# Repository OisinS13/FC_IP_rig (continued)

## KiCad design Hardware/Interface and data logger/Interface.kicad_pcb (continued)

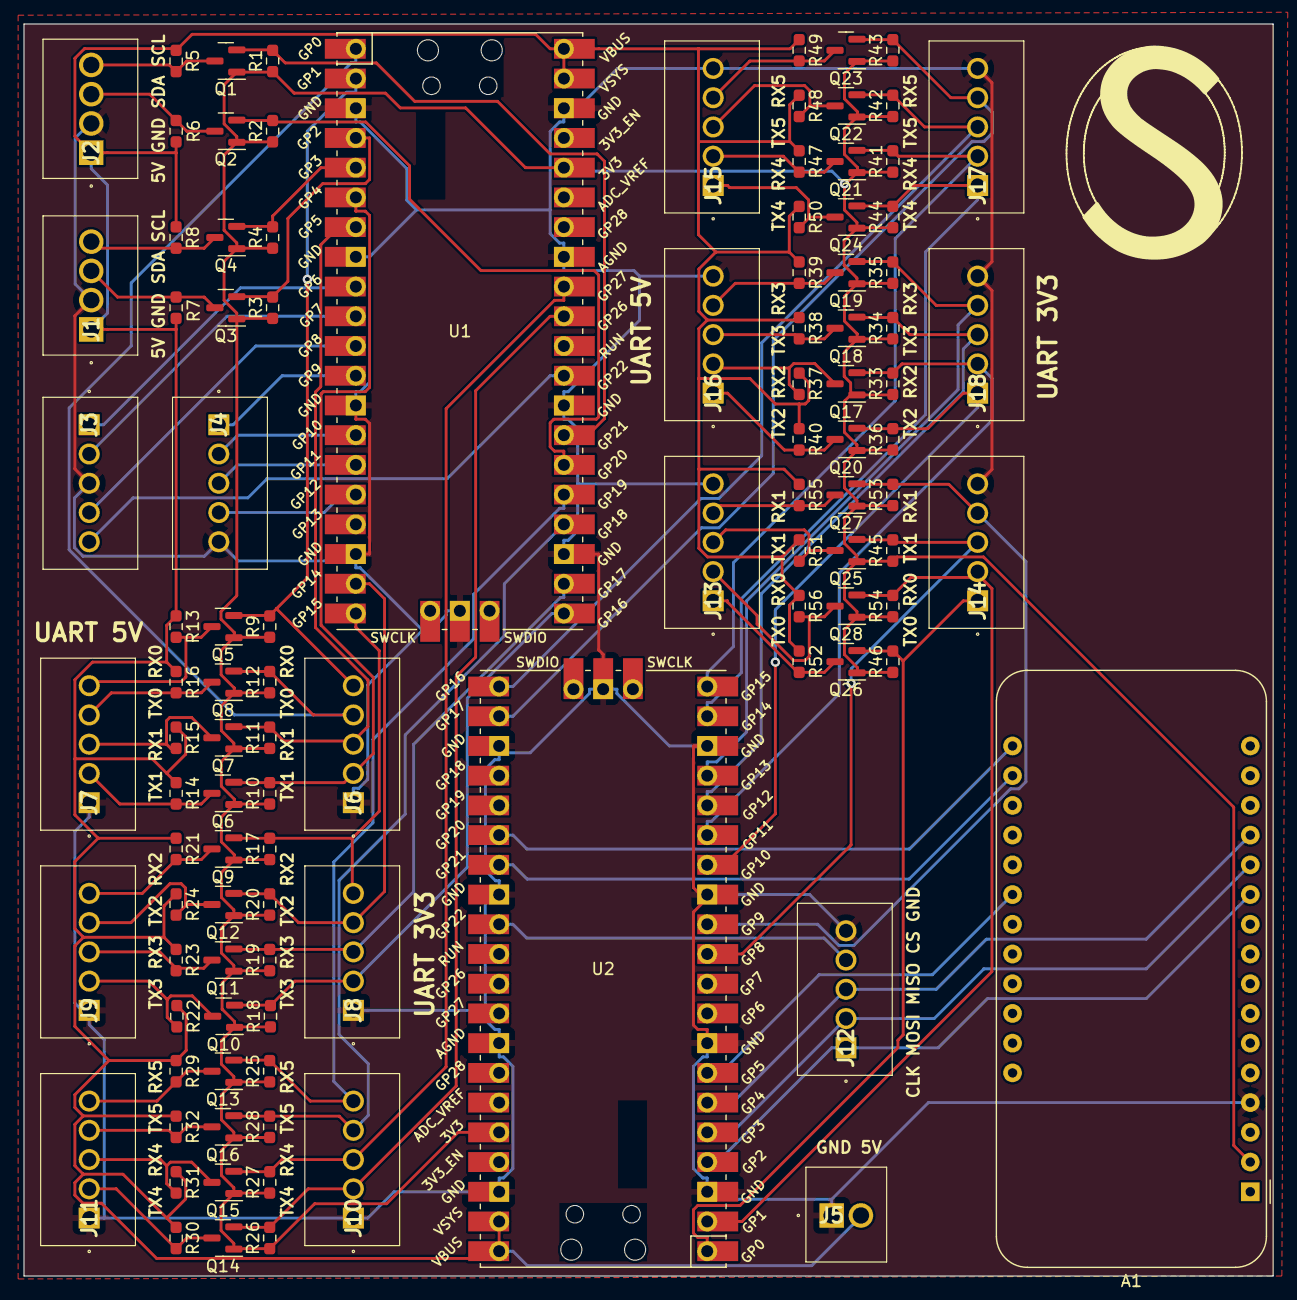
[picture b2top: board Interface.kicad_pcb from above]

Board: 2 copper layers, 106.8 x 107.0 mm, 105 parts (0 on the bottom side), 74 nets.

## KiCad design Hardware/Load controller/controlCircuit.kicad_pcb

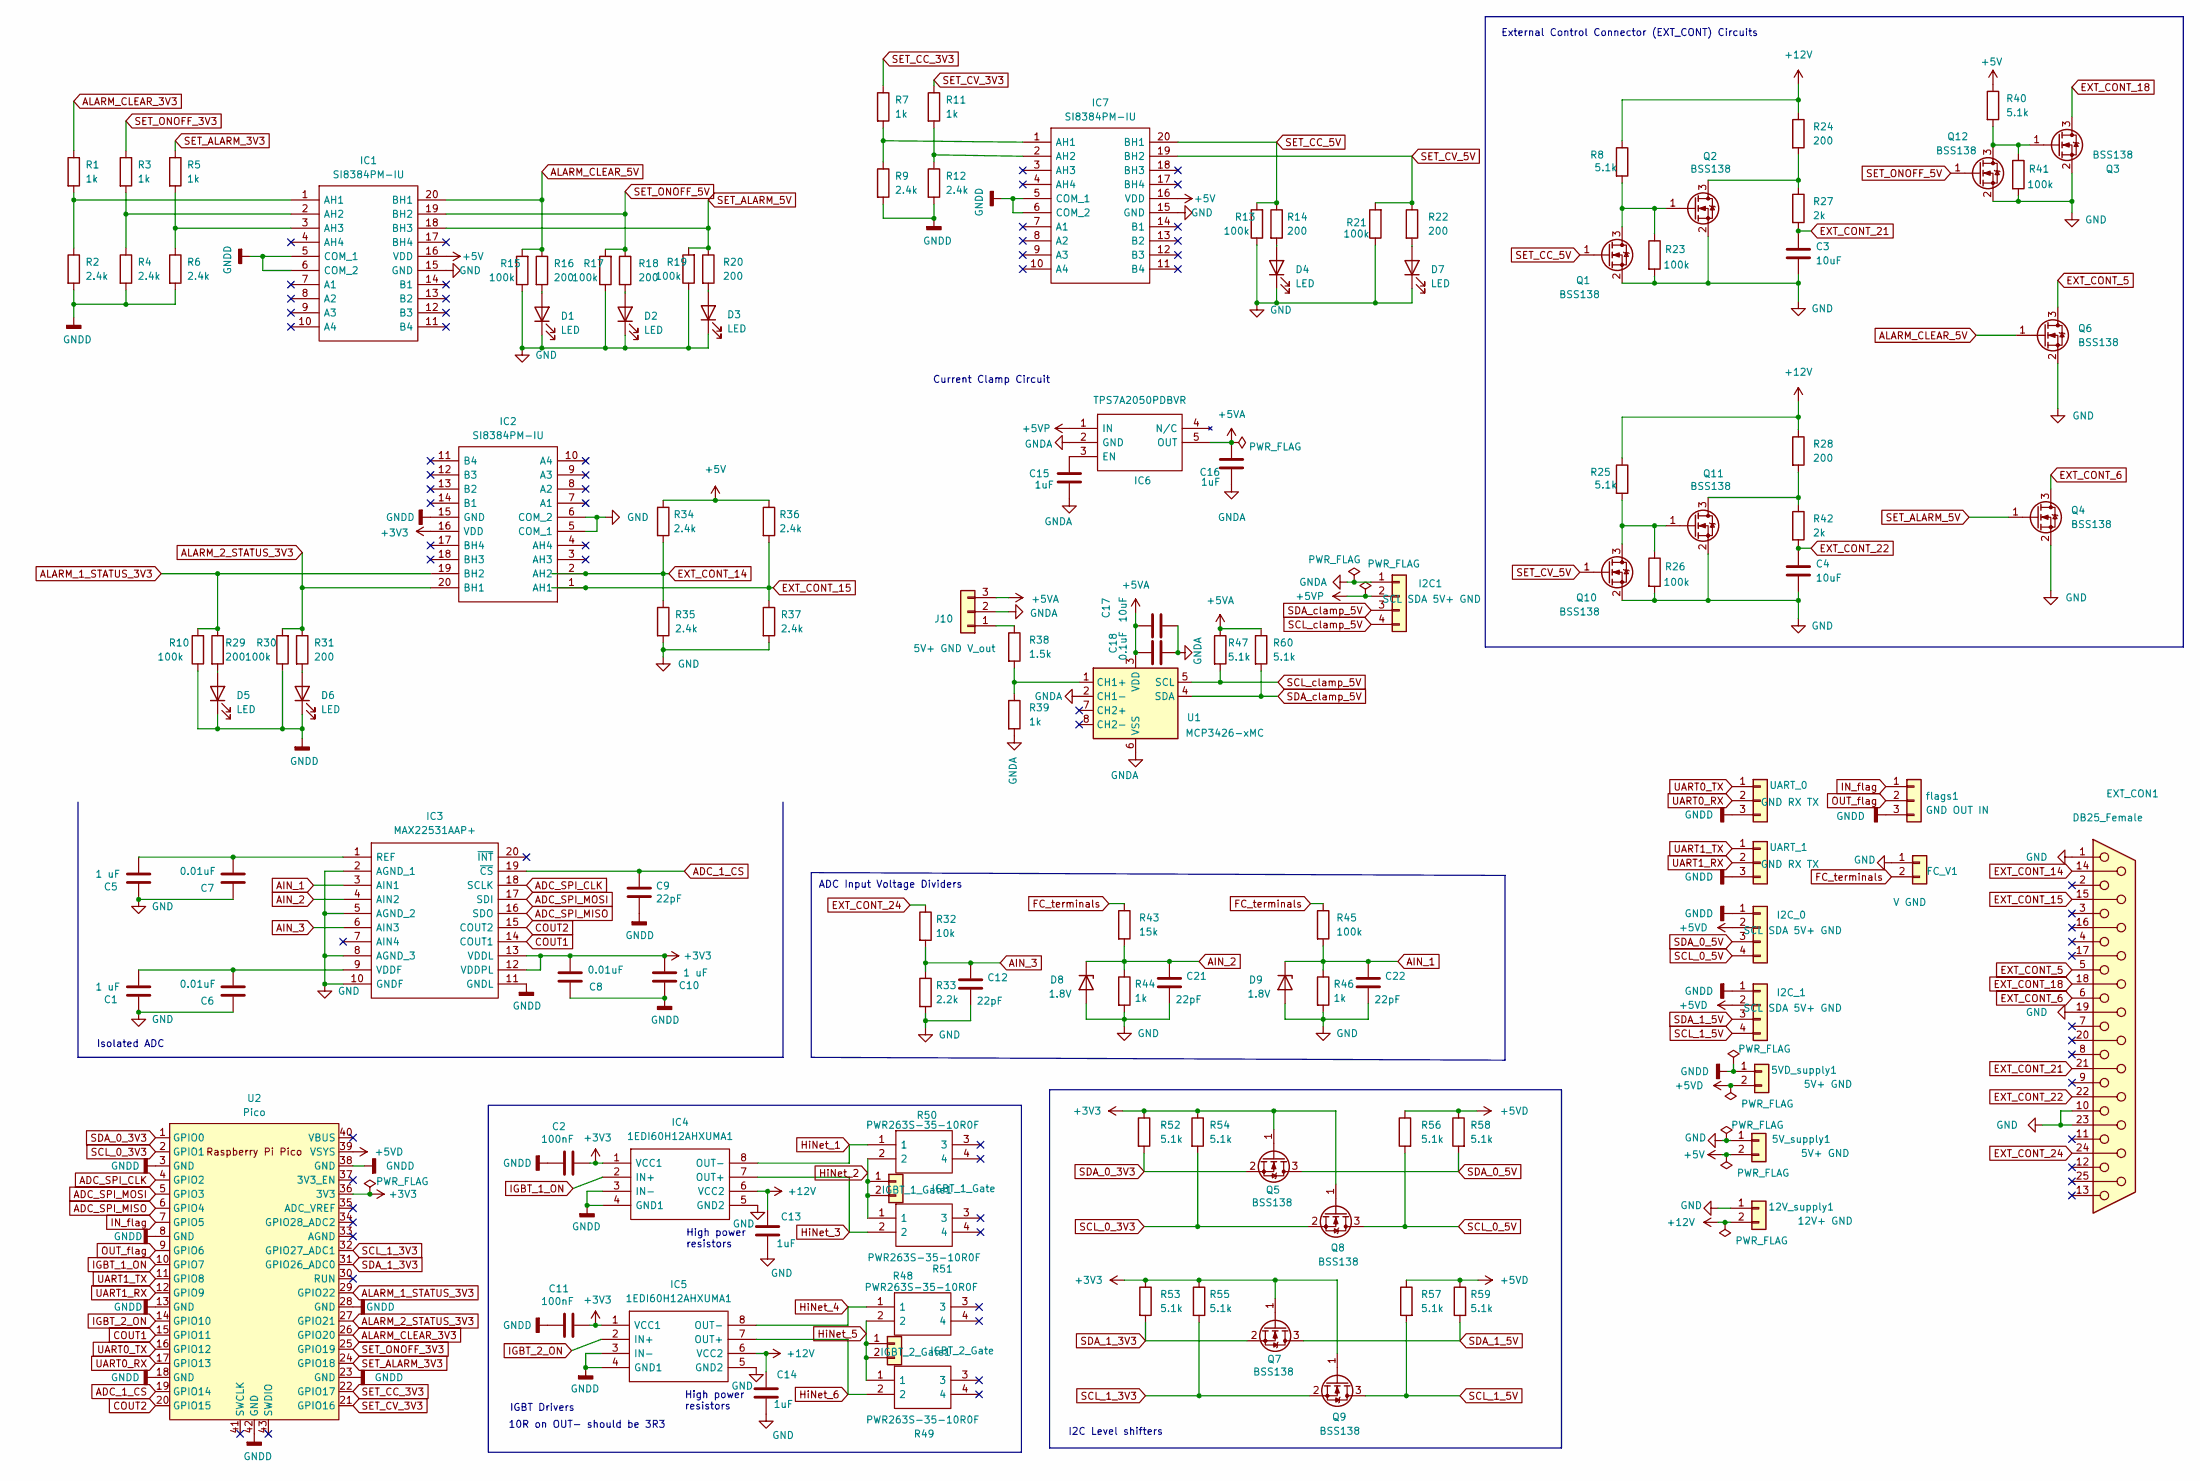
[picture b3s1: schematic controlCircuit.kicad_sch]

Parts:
5VD_supply1, 5V_supply1: 5V+ GND; 1963531
12V_supply1: 12V+ GND; 1963531
C1, C5, C10: 1 uF; C_0603_1608Metric_Pad1.08x0.95mm_HandSolder
C2, C11: 100nF; C_0603_1608Metric_Pad1.08x0.95mm_HandSolder
C3, C4: 10uF; CP_Radial_D4.0mm_P2.00mm
C6, C7, C8: 0.01uF; C_0603_1608Metric_Pad1.08x0.95mm_HandSolder
C9, C12, C21, C22: 22pF; C_0603_1608Metric_Pad1.08x0.95mm_HandSolder
C13, C14, C15, C16: 1uF; C_0603_1608Metric_Pad1.08x0.95mm_HandSolder
C17: 10uF; C_0603_1608Metric_Pad1.08x0.95mm_HandSolder
C18: 0.1uF; C_0603_1608Metric_Pad1.08x0.95mm_HandSolder
D1, D2, D3, D4, D5, D6, D7: LED; LED_0603_1608Metric_Pad1.05x0.95mm_HandSolder
D8, D9: 1.8V; SOD3716X135N
EXT_CON1: DB25_Female; ID25S33E4GX00LF
FC_V1: V GND; 1963531
I2C1, I2C_0, I2C_1: SCL SDA 5V+ GND; 1963557
IC1, IC2, IC7: SI8384PM-IU; SOP64P600X175-20N; Mouser Part Number 634-SI8384PM-IU
IC3: MAX22531AAP+; SOP65P778X199-20N; Mouser Part Number 700-MAX22531AAP+
IC4, IC5: 1EDI60H12AHXUMA1; SOIC127P1030X265-8N; Mouser Part Number 726-1EDI60H12AHXUMA1
IC6: TPS7A2050PDBVR; SOT95P280X145-5N; Mouser Part Number 595-TPS7A2050PDBVR
IGBT_1_Gate1: IGBT_1_Gate; 1963531
IGBT_2_Gate1: IGBT_2_Gate; 1963531
J10: 5V+ GND V_out; L06P400S05_footprint
Q1, Q2, Q3, Q4, Q5, Q6, Q7, Q8, Q9, Q10, Q11, Q12: BSS138; SOT-23
R1, R3, R5, R7, R11, R39, R44, R46: 1k; R_0603_1608Metric_Pad0.98x0.95mm_HandSolder
R2, R4, R6, R9, R12, R34, R35, R36, R37: 2.4k; R_0603_1608Metric_Pad0.98x0.95mm_HandSolder
R8, R25, R40, R47, R52, R53, R54, R55, R56, R57, R58, R59, R60: 5.1k; R_0603_1608Metric_Pad0.98x0.95mm_HandSolder
R10, R13, R15, R17, R19, R21, R23, R26, R30, R41, R45: 100k; R_0603_1608Metric_Pad0.98x0.95mm_HandSolder
R14, R16, R18, R20, R22, R24, R28, R29, R31: 200; R_0603_1608Metric_Pad0.98x0.95mm_HandSolder
R27, R42: 2k; R_0603_1608Metric_Pad0.98x0.95mm_HandSolder
R32: 10k; R_0603_1608Metric_Pad0.98x0.95mm_HandSolder
R33: 2.2k; R_0603_1608Metric_Pad0.98x0.95mm_HandSolder
R38: 1.5k; R_0603_1608Metric_Pad0.98x0.95mm_HandSolder
R43: 15k; R_0603_1608Metric_Pad0.98x0.95mm_HandSolder
R48, R49, R50, R51: PWR263S-35-10R0F; PWR263S3510R0F; Mouser Part Number 652-PWR263S3510R0F
U1: MCP3426-xMC; DFN-8-1EP_3x2mm_P0.5mm_EP1.75x1.45mm
U2: Pico; RPi_Pico_SMD_TH
UART_0, UART_1: GND RX TX; 1963544
flags1: GND OUT IN; 1963544

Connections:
+3V3: C2.2, C8.2, C10.1, C11.2, IC2.16 (VDD), IC3.12 (VDDPL), IC3.13 (VDDL), IC4.1 (VCC1), IC5.1 (VCC1), Q5.1 (G), Q7.1 (G), Q8.1 (G), Q9.1 (G), R52.1, R53.1, R54.1, R55.1, U2.36 (3V3)
+5V: 5V_supply1.2, IC1.16 (VDD), IC7.16 (VDD), R34.1, R36.1, R40.1
+5VA: C16.1, C17.1, C18.1, IC6.5 (OUT), J10.3, R47.1, R60.1, U1.3 (VDD)
+5VD: 5VD_supply1.2, I2C_0.2, I2C_1.2, R56.1, R57.1, R58.1, R59.1, U2.39 (VSYS)
+5VP: I2C1.2, IC6.1 (IN)
+12V: 12V_supply1.2, C13.1, C14.1, IC4.6 (VCC2), IC5.6 (VCC2), R8.1, R24.1, R25.1, R28.1
ADC_1_CS: C9.1, IC3.19 (~CS), U2.19 (GPIO14)
ADC_SPI_CLK: IC3.18 (SCLK), U2.4 (GPIO2)
ADC_SPI_MISO: IC3.16 (SDO), U2.6 (GPIO4)
ADC_SPI_MOSI: IC3.17 (SDI), U2.5 (GPIO3)
AIN_1: C22.1, D9.1 (K), IC3.3 (AIN1), R45.2, R46.1
AIN_2: C21.1, D8.1 (K), IC3.4 (AIN2), R43.2, R44.1
AIN_3: C12.1, IC3.6 (AIN3), R32.2, R33.1
ALARM_1_STATUS_3V3: IC2.19 (BH2), R10.2, R29.1, U2.29 (GPIO22)
ALARM_2_STATUS_3V3: IC2.20 (BH1), R30.2, R31.1, U2.27 (GPIO21)
ALARM_CLEAR_3V3: R1.1, U2.26 (GPIO20)
ALARM_CLEAR_5V: IC1.20 (BH1), Q6.1 (G), R15.2, R16.1
COUT1: IC3.14 (COUT1), U2.15 (GPIO11)
COUT2: IC3.15 (COUT2), U2.20 (GPIO15)
EXT_CONT_5: EXT_CON1.5, Q6.3 (D)
EXT_CONT_6: EXT_CON1.6, Q4.3 (D)
EXT_CONT_14: EXT_CON1.14, IC2.2 (AH2), R34.2, R35.1
EXT_CONT_15: EXT_CON1.15, IC2.1 (AH1), R36.2, R37.1
EXT_CONT_18: EXT_CON1.18, Q3.3 (D)
EXT_CONT_21: C3.1, EXT_CON1.21, R27.2
EXT_CONT_22: C4.1, EXT_CON1.22, R42.2
EXT_CONT_24: EXT_CON1.24, R32.1
FC_terminals: FC_V1.2, R43.1, R45.1
GND: 5V_supply1.1, 12V_supply1.1, C1.2, C3.2, C4.2, C5.2, C6.1, C7.1, C12.2, C13.2, C14.2, C21.2, C22.2, D1.1 (K), D2.1 (K), D3.1 (K), D4.1 (K), D7.1 (K), D8.2 (A), D9.2 (A), EXT_CON1.1, EXT_CON1.10, EXT_CON1.19, EXT_CON1.23, FC_V1.1, IC1.15 (GND), IC2.5 (COM_1), IC2.6 (COM_2), IC3.2 (AGND_1), IC3.5 (AGND_2), IC3.8 (AGND_3), IC3.10 (GNDF), IC4.5 (GND2), IC5.5 (GND2), IC7.15 (GND), Q1.2 (S), Q2.2 (S), Q3.2 (S), Q4.2 (S), Q6.2 (S), Q10.2 (S), Q11.2 (S), Q12.2 (S), R13.1, R15.1, R17.1, R19.1, R21.1, R23.2, R26.2, R33.2, R35.2, R37.2, R41.2, R44.2, R46.2
GNDA: C15.2, C16.2, C17.2, C18.2, I2C1.1, IC6.2 (GND), J10.2, R39.2, U1.2 (CH1-), U1.6 (VSS), U1.9 (VSS)
GNDD: 5VD_supply1.1, C2.1, C8.1, C9.2, C10.2, C11.1, D5.1 (K), D6.1 (K), I2C_0.1, I2C_1.1, IC1.5 (COM_1), IC1.6 (COM_2), IC2.15 (GND), IC3.11 (GNDL), IC4.3 (IN-), IC4.4 (GND1), IC5.3 (IN-), IC5.4 (GND1), IC7.5 (COM_1), IC7.6 (COM_2), R2.2, R4.2, R6.2, R9.2, R10.1, R12.2, R30.1, U2.3 (GND), U2.8 (GND), U2.13 (GND), U2.18 (GND), U2.23 (GND), U2.28 (GND), U2.38 (GND), U2.42 (GND), UART_0.3, UART_1.3, flags1.3
HiNet_1: IC4.8 (OUT-), R50.1
HiNet_2: IGBT_1_Gate1.1, IGBT_1_Gate1.2, R50.2, R51.1
HiNet_3: IC4.7 (OUT+), R51.2
HiNet_4: IC5.8 (OUT-), R48.1
HiNet_5: IGBT_2_Gate1.1, IGBT_2_Gate1.2, R48.2, R49.1
HiNet_6: IC5.7 (OUT+), R49.2
IGBT_1_ON: IC4.2 (IN+), U2.10 (GPIO7)
IGBT_2_ON: IC5.2 (IN+), U2.14 (GPIO10)
IN_flag: U2.7 (GPIO5), flags1.1
unnamed: C1.1, C6.2, IC3.9 (VDDF)
unnamed: C5.1, C7.2, IC3.1 (REF)
unnamed: C15.1, IC6.3 (EN)
unnamed: D1.2 (A), R16.2
unnamed: D2.2 (A), R18.2
unnamed: D3.2 (A), R20.2
unnamed: D4.2 (A), R14.2
unnamed: D5.2 (A), R29.2
unnamed: D6.2 (A), R31.2
unnamed: D7.2 (A), R22.2
unnamed: IC1.1 (AH1), R1.2, R2.1
unnamed: IC1.2 (AH2), R3.2, R4.1
unnamed: IC1.3 (AH3), R5.2, R6.1
unnamed: IC7.1 (AH1), R7.2, R9.1
unnamed: IC7.2 (AH2), R11.2, R12.1
unnamed: J10.1, R38.1
unnamed: Q1.3 (D), Q2.1 (G), R8.2, R23.1
unnamed: Q2.3 (D), R24.2, R27.1
unnamed: Q10.3 (D), Q11.1 (G), R25.2, R26.1
unnamed: Q11.3 (D), R28.2, R42.1
unnamed: Q3.1 (G), Q12.3 (D), R40.2, R41.1
unnamed: R38.2, R39.1, U1.1 (CH1+)
OUT_flag: U2.9 (GPIO6), flags1.2
SCL_0_3V3: Q8.2 (S), R54.2, U2.2 (GPIO1)
SCL_0_5V: I2C_0.4, Q8.3 (D), R56.2
SCL_1_3V3: Q9.2 (S), R55.2, U2.32 (GPIO27_ADC1)
SCL_1_5V: I2C_1.4, Q9.3 (D), R57.2
SCL_clamp_5V: I2C1.4, R47.2, U1.5 (SCL)
SDA_0_3V3: Q5.2 (S), R52.2, U2.1 (GPIO0)
SDA_0_5V: I2C_0.3, Q5.3 (D), R58.2
SDA_1_3V3: Q7.2 (S), R53.2, U2.31 (GPIO26_ADC0)
SDA_1_5V: I2C_1.3, Q7.3 (D), R59.2
SDA_clamp_5V: I2C1.3, R60.2, U1.4 (SDA)
SET_ALARM_3V3: R5.1, U2.24 (GPIO18)
SET_ALARM_5V: IC1.18 (BH3), Q4.1 (G), R19.2, R20.1
SET_CC_3V3: R7.1, U2.22 (GPIO17)
SET_CC_5V: IC7.20 (BH1), Q1.1 (G), R13.2, R14.1
SET_CV_3V3: R11.1, U2.21 (GPIO16)
SET_CV_5V: IC7.19 (BH2), Q10.1 (G), R21.2, R22.1
SET_ONOFF_3V3: R3.1, U2.25 (GPIO19)
SET_ONOFF_5V: IC1.19 (BH2), Q12.1 (G), R17.2, R18.1
UART0_RX: U2.17 (GPIO13), UART_0.2
UART0_TX: U2.16 (GPIO12), UART_0.1
UART1_RX: U2.12 (GPIO9), UART_1.2
UART1_TX: U2.11 (GPIO8), UART_1.1

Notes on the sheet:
Current Clamp Circuit
High power resistors
External Control Connector (EXT_CONT) Circuits
Isolated ADC
IGBT Drivers
ADC Input Voltage Dividers
I2C Level shifters
10R on OUT- should be 3R3

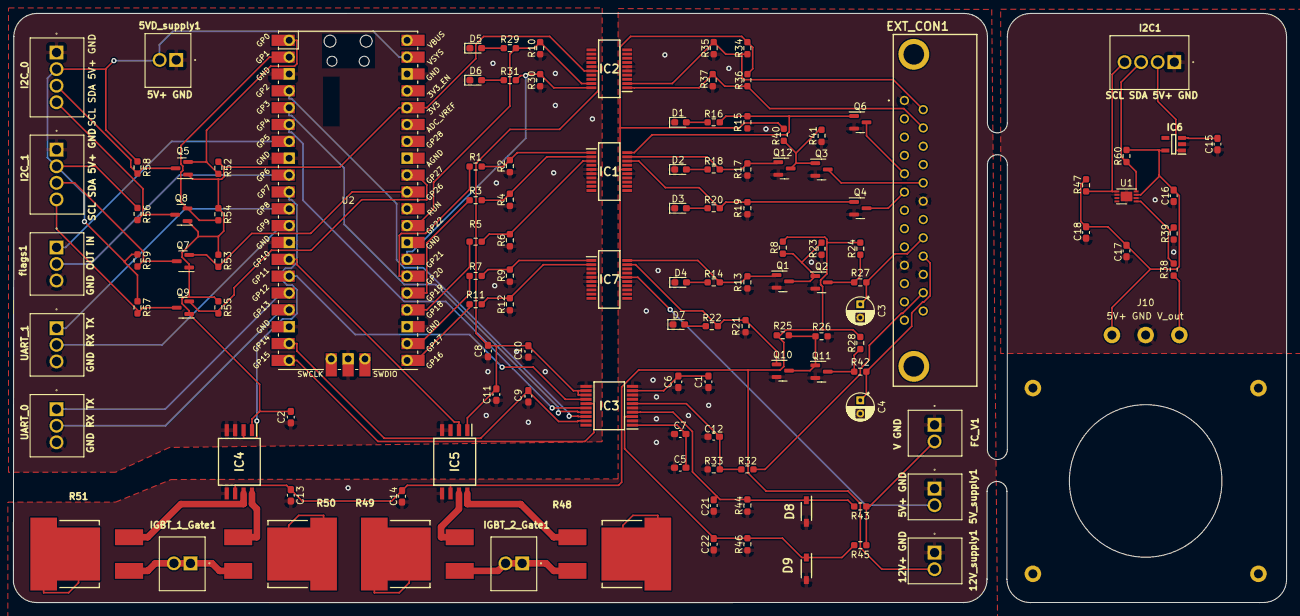
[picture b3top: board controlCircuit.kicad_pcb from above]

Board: 2 copper layers, 191.9 x 88.7 mm, 124 parts (0 on the bottom side), 85 nets.

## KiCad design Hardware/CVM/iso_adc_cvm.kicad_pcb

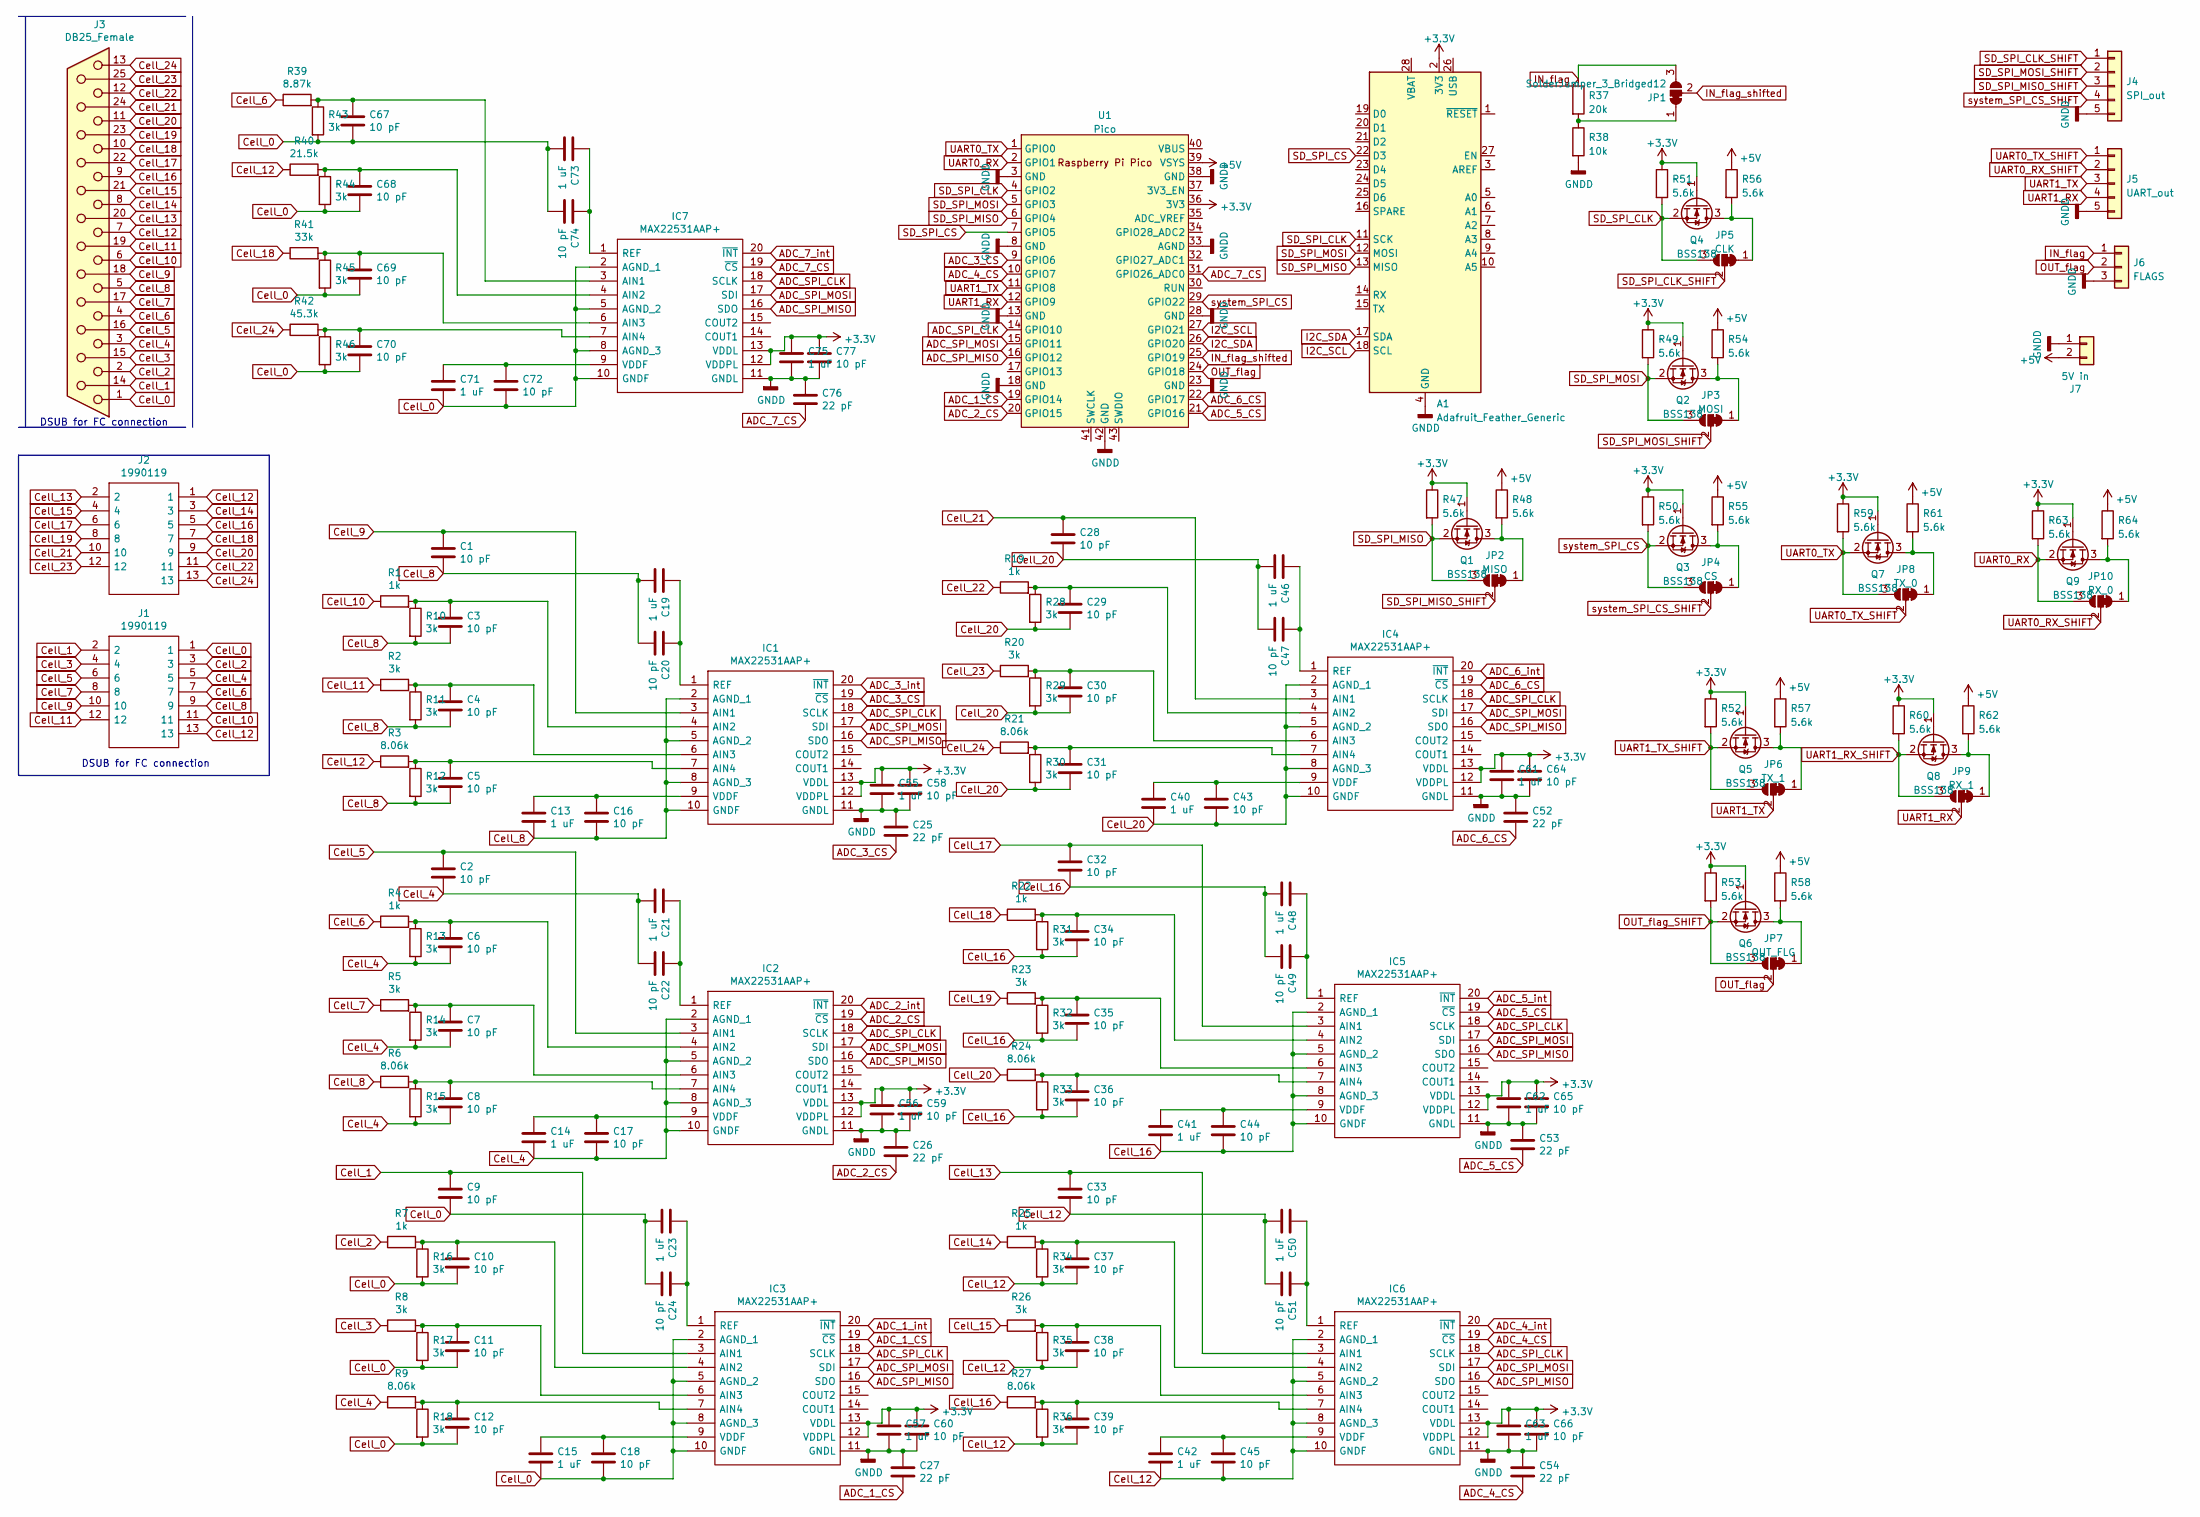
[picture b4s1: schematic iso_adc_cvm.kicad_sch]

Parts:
A1: Adafruit_Feather_Generic; Adafruit_Feather
C1, C2, C3, C4, C5, C6, C7, C8, C9, C10, C11, C12, C16, C17, C18, C20, C22, C24, C28, C29, C30, C31, C32, C33, C34, C35, C36, C37, C38, C39, C43, C44, C45, C47, C49, C51, C58, C59, C60, C64, C65, C66, C67, C68, C69, C70, C72, C74, C77: 10 pF; C_0603_1608Metric_Pad1.08x0.95mm_HandSolder
C13, C14, C15, C19, C21, C23, C40, C41, C42, C46, C48, C50, C55, C56, C57, C61, C62, C63, C71, C73, C75: 1 uF; C_0603_1608Metric_Pad1.08x0.95mm_HandSolder
C25, C26, C27, C52, C53, C54, C76: 22 pF; C_0603_1608Metric_Pad1.08x0.95mm_HandSolder
IC1, IC2, IC3, IC4, IC5, IC6, IC7: MAX22531AAP+; SOP65P778X199-20N; Mouser Part Number 700-MAX22531AAP+
J1, J2: 1990119; Mouser Part Number 651-1990119
J3: DB25_Female; DSUB-25_Female_Horizontal_P2.77x2.84mm_EdgePinOffset9.90mm_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
J4: SPI_out; 1881587
J5: UART_out; 1881587
J6: FLAGS; 1963544
J7: 5V in; 1963531
JP1: SolderJumper_3_Bridged12; SolderJumper-3_P1.3mm_Bridged2Bar12_RoundedPad1.0x1.5mm
JP2: MISO; SolderJumper-3_P1.3mm_Bridged2Bar12_RoundedPad1.0x1.5mm
JP3: MOSI; SolderJumper-3_P1.3mm_Bridged2Bar12_RoundedPad1.0x1.5mm
JP4: CS; SolderJumper-3_P1.3mm_Bridged2Bar12_RoundedPad1.0x1.5mm
JP5: CLK; SolderJumper-3_P1.3mm_Bridged2Bar12_RoundedPad1.0x1.5mm
JP6: TX_1; SolderJumper-3_P1.3mm_Bridged2Bar12_RoundedPad1.0x1.5mm
JP7: OUT_FLG; SolderJumper-3_P1.3mm_Bridged2Bar12_RoundedPad1.0x1.5mm
JP8: TX_0; SolderJumper-3_P1.3mm_Bridged2Bar12_RoundedPad1.0x1.5mm
JP9: RX_1; SolderJumper-3_P1.3mm_Bridged2Bar12_RoundedPad1.0x1.5mm
JP10: RX_0; SolderJumper-3_P1.3mm_Bridged2Bar12_RoundedPad1.0x1.5mm
Q1, Q2, Q3, Q4, Q5, Q6, Q7, Q8, Q9: BSS138; SOT-23
R1, R4, R7, R19, R22, R25: 1k; R_0603_1608Metric_Pad0.98x0.95mm_HandSolder
R2, R5, R8, R10, R11, R12, R13, R14, R15, R16, R17, R18, R20, R23, R26, R28, R29, R30, R31, R32, R33, R34, R35, R36, R43, R44, R45, R46: 3k; R_0603_1608Metric_Pad0.98x0.95mm_HandSolder
R3, R6, R9, R21, R24, R27: 8.06k; R_0603_1608Metric_Pad0.98x0.95mm_HandSolder
R37: 20k; R_0603_1608Metric_Pad0.98x0.95mm_HandSolder
R38: 10k; R_0603_1608Metric_Pad0.98x0.95mm_HandSolder
R39: 8.87k; R_0603_1608Metric_Pad0.98x0.95mm_HandSolder
R40: 21.5k; R_0603_1608Metric_Pad0.98x0.95mm_HandSolder
R41: 33k; R_0603_1608Metric_Pad0.98x0.95mm_HandSolder
R42: 45.3k; R_0603_1608Metric_Pad0.98x0.95mm_HandSolder
R47, R48, R49, R50, R51, R52, R53, R54, R55, R56, R57, R58, R59, R60, R61, R62, R63, R64: 5.6k; R_0603_1608Metric_Pad0.98x0.95mm_HandSolder
U1: Pico; RPi_Pico_SMD_TH

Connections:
+3.3V: A1.2 (3V3), C55.1, C56.1, C57.1, C58.1, C59.1, C60.1, C61.1, C62.1, C63.1, C64.1, C65.1, C66.1, C75.1, C77.1, IC1.12 (VDDPL), IC1.13 (VDDL), IC2.12 (VDDPL), IC2.13 (VDDL), IC3.12 (VDDPL), IC3.13 (VDDL), IC4.12 (VDDPL), IC4.13 (VDDL), IC5.12 (VDDPL), IC5.13 (VDDL), IC6.12 (VDDPL), IC6.13 (VDDL), IC7.12 (VDDPL), IC7.13 (VDDL), Q1.1 (G), Q2.1 (G), Q3.1 (G), Q4.1 (G), Q5.1 (G), Q6.1 (G), Q7.1 (G), Q8.1 (G), Q9.1 (G), R47.1, R49.1, R50.1, R51.1, R52.1, R53.1, R59.1, R60.1, R63.1, U1.36 (3V3)
+5V: J7.2, R48.1, R54.1, R55.1, R56.1, R57.1, R58.1, R61.1, R62.1, R64.1, U1.39 (VSYS)
ADC_1_CS: C27.2, IC3.19 (~CS), U1.19 (GPIO14)
ADC_1_int: IC3.20 (~INT)
ADC_2_CS: C26.2, IC2.19 (~CS), U1.20 (GPIO15)
ADC_2_int: IC2.20 (~INT)
ADC_3_CS: C25.2, IC1.19 (~CS), U1.9 (GPIO6)
ADC_3_int: IC1.20 (~INT)
ADC_4_CS: C54.2, IC6.19 (~CS), U1.10 (GPIO7)
ADC_4_int: IC6.20 (~INT)
ADC_5_CS: C53.2, IC5.19 (~CS), U1.21 (GPIO16)
ADC_5_int: IC5.20 (~INT)
ADC_6_CS: C52.2, IC4.19 (~CS), U1.22 (GPIO17)
ADC_6_int: IC4.20 (~INT)
ADC_7_CS: C76.2, IC7.19 (~CS), U1.31 (GPIO26_ADC0)
ADC_7_int: IC7.20 (~INT)
ADC_SPI_CLK: IC1.18 (SCLK), IC2.18 (SCLK), IC3.18 (SCLK), IC4.18 (SCLK), IC5.18 (SCLK), IC6.18 (SCLK), IC7.18 (SCLK), U1.14 (GPIO10)
ADC_SPI_MISO: IC1.16 (SDO), IC2.16 (SDO), IC3.16 (SDO), IC4.16 (SDO), IC5.16 (SDO), IC6.16 (SDO), IC7.16 (SDO), U1.16 (GPIO12)
ADC_SPI_MOSI: IC1.17 (SDI), IC2.17 (SDI), IC3.17 (SDI), IC4.17 (SDI), IC5.17 (SDI), IC6.17 (SDI), IC7.17 (SDI), U1.15 (GPIO11)
Cell_0: C9.2, C10.2, C11.2, C12.2, C15.2, C18.2, C23.2, C24.2, C67.2, C68.2, C69.2, C70.2, C71.2, C72.2, C73.2, C74.2, IC3.2 (AGND_1), IC3.5 (AGND_2), IC3.8 (AGND_3), IC3.10 (GNDF), IC7.2 (AGND_1), IC7.5 (AGND_2), IC7.8 (AGND_3), IC7.10 (GNDF), J1.1, J3.1, R16.2, R17.2, R18.2, R43.2, R44.2, R45.2, R46.2
Cell_1: C9.1, IC3.3 (AIN1), J1.2, J3.14
Cell_2: J1.3, J3.2, R7.1
Cell_3: J1.4, J3.15, R8.1
Cell_4: C2.2, C6.2, C7.2, C8.2, C14.2, C17.2, C21.2, C22.2, IC2.2 (AGND_1), IC2.5 (AGND_2), IC2.8 (AGND_3), IC2.10 (GNDF), J1.5, J3.3, R9.1, R13.2, R14.2, R15.2
Cell_5: C2.1, IC2.3 (AIN1), J1.6, J3.16
Cell_6: J1.7, J3.4, R4.1, R39.1
Cell_7: J1.8, J3.17, R5.1
Cell_8: C1.2, C3.2, C4.2, C5.2, C13.2, C16.2, C19.2, C20.2, IC1.2 (AGND_1), IC1.5 (AGND_2), IC1.8 (AGND_3), IC1.10 (GNDF), J1.9, J3.5, R6.1, R10.2, R11.2, R12.2
Cell_9: C1.1, IC1.3 (AIN1), J1.10, J3.18
Cell_10: J1.11, J3.6, R1.1
Cell_11: J1.12, J3.19, R2.1
Cell_12: C33.2, C37.2, C38.2, C39.2, C42.2, C45.2, C50.2, C51.2, IC6.2 (AGND_1), IC6.5 (AGND_2), IC6.8 (AGND_3), IC6.10 (GNDF), J1.13, J2.1, J3.7, R3.1, R34.2, R35.2, R36.2, R40.1
Cell_13: C33.1, IC6.3 (AIN1), J2.2, J3.20
Cell_14: J2.3, J3.8, R25.1
Cell_15: J2.4, J3.21, R26.1
Cell_16: C32.2, C34.2, C35.2, C36.2, C41.2, C44.2, C48.2, C49.2, IC5.2 (AGND_1), IC5.5 (AGND_2), IC5.8 (AGND_3), IC5.10 (GNDF), J2.5, J3.9, R27.1, R31.2, R32.2, R33.2
Cell_17: C32.1, IC5.3 (AIN1), J2.6, J3.22
Cell_18: J2.7, J3.10, R22.1, R41.1
Cell_19: J2.8, J3.23, R23.1
Cell_20: C28.2, C29.2, C30.2, C31.2, C40.2, C43.2, C46.2, C47.2, IC4.2 (AGND_1), IC4.5 (AGND_2), IC4.8 (AGND_3), IC4.10 (GNDF), J2.9, J3.11, R24.1, R28.2, R29.2, R30.2
Cell_21: C28.1, IC4.3 (AIN1), J2.10, J3.24
Cell_22: J2.11, J3.12, R19.1
Cell_23: J2.12, J3.25, R20.1
Cell_24: J2.13, J3.13, R21.1, R42.1
GNDD: A1.4 (GND), C25.1, C26.1, C27.1, C52.1, C53.1, C54.1, C55.2, C56.2, C57.2, C58.2, C59.2, C60.2, C61.2, C62.2, C63.2, C64.2, C65.2, C66.2, C75.2, C76.1, C77.2, IC1.11 (GNDL), IC2.11 (GNDL), IC3.11 (GNDL), IC4.11 (GNDL), IC5.11 (GNDL), IC6.11 (GNDL), IC7.11 (GNDL), J4.5, J5.5, J6.3, J7.1, R38.2, U1.3 (GND), U1.8 (GND), U1.13 (GND), U1.18 (GND), U1.23 (GND), U1.28 (GND), U1.33 (AGND), U1.38 (GND), U1.42 (GND)
I2C_SCL: A1.18 (SCL), U1.27 (GPIO21)
I2C_SDA: A1.17 (SDA), U1.26 (GPIO20)
IN_flag: J6.1, JP1.3 (B), R37.1
IN_flag_shifted: JP1.2 (C), U1.25 (GPIO19)
unnamed: C3.1, IC1.4 (AIN2), R1.2, R10.1
unnamed: C4.1, IC1.6 (AIN3), R2.2, R11.1
unnamed: C5.1, IC1.7 (AIN4), R3.2, R12.1
unnamed: C6.1, IC2.4 (AIN2), R4.2, R13.1
unnamed: C7.1, IC2.6 (AIN3), R5.2, R14.1
unnamed: C8.1, IC2.7 (AIN4), R6.2, R15.1
unnamed: C10.1, IC3.4 (AIN2), R7.2, R16.1
unnamed: C11.1, IC3.6 (AIN3), R8.2, R17.1
unnamed: C12.1, IC3.7 (AIN4), R9.2, R18.1
unnamed: C13.1, C16.1, IC1.9 (VDDF)
unnamed: C14.1, C17.1, IC2.9 (VDDF)
unnamed: C15.1, C18.1, IC3.9 (VDDF)
unnamed: C19.1, C20.1, IC1.1 (REF)
unnamed: C21.1, C22.1, IC2.1 (REF)
unnamed: C23.1, C24.1, IC3.1 (REF)
unnamed: C29.1, IC4.4 (AIN2), R19.2, R28.1
unnamed: C30.1, IC4.6 (AIN3), R20.2, R29.1
unnamed: C31.1, IC4.7 (AIN4), R21.2, R30.1
unnamed: C34.1, IC5.4 (AIN2), R22.2, R31.1
unnamed: C35.1, IC5.6 (AIN3), R23.2, R32.1
unnamed: C36.1, IC5.7 (AIN4), R24.2, R33.1
unnamed: C37.1, IC6.4 (AIN2), R25.2, R34.1
unnamed: C38.1, IC6.6 (AIN3), R26.2, R35.1
unnamed: C39.1, IC6.7 (AIN4), R27.2, R36.1
unnamed: C40.1, C43.1, IC4.9 (VDDF)
unnamed: C41.1, C44.1, IC5.9 (VDDF)
unnamed: C42.1, C45.1, IC6.9 (VDDF)
unnamed: C46.1, C47.1, IC4.1 (REF)
unnamed: C48.1, C49.1, IC5.1 (REF)
unnamed: C50.1, C51.1, IC6.1 (REF)
unnamed: C67.1, IC7.3 (AIN1), R39.2, R43.1
unnamed: C68.1, IC7.4 (AIN2), R40.2, R44.1
unnamed: C69.1, IC7.6 (AIN3), R41.2, R45.1
unnamed: C70.1, IC7.7 (AIN4), R42.2, R46.1
unnamed: C71.1, C72.1, IC7.9 (VDDF)
unnamed: C73.1, C74.1, IC7.1 (REF)
unnamed: JP1.1 (A), R37.2, R38.1
unnamed: JP2.1 (A), Q1.3 (D), R48.2
unnamed: JP3.1 (A), Q2.3 (D), R54.2
unnamed: JP4.1 (A), Q3.3 (D), R55.2
unnamed: JP5.1 (A), Q4.3 (D), R56.2
unnamed: JP6.1 (A), Q5.3 (D), R57.2
unnamed: JP7.1 (A), Q6.3 (D), R58.2
unnamed: JP8.1 (A), Q7.3 (D), R61.2
unnamed: JP9.1 (A), Q8.3 (D), R62.2
unnamed: JP10.1 (A), Q9.3 (D), R64.2
OUT_flag: J6.2, JP7.2 (C), U1.24 (GPIO18)
OUT_flag_SHIFT: JP7.3 (B), Q6.2 (S), R53.2
SD_SPI_CLK: A1.11 (SCK), JP5.3 (B), Q4.2 (S), R51.2, U1.4 (GPIO2)
SD_SPI_CLK_SHIFT: J4.1, JP5.2 (C)
SD_SPI_CS: A1.22 (D3), U1.7 (GPIO5)
SD_SPI_MISO: A1.13 (MISO), JP2.3 (B), Q1.2 (S), R47.2, U1.6 (GPIO4)
SD_SPI_MISO_SHIFT: J4.3, JP2.2 (C)
SD_SPI_MOSI: A1.12 (MOSI), JP3.3 (B), Q2.2 (S), R49.2, U1.5 (GPIO3)
SD_SPI_MOSI_SHIFT: J4.2, JP3.2 (C)
UART0_RX: JP10.3 (B), Q9.2 (S), R63.2, U1.2 (GPIO1)
UART0_RX_SHIFT: J5.2, JP10.2 (C)
UART0_TX: JP8.3 (B), Q7.2 (S), R59.2, U1.1 (GPIO0)
UART0_TX_SHIFT: J5.1, JP8.2 (C)
UART1_RX: J5.4, JP9.2 (C), U1.12 (GPIO9)
UART1_RX_SHIFT: JP9.3 (B), Q8.2 (S), R60.2
UART1_TX: J5.3, JP6.2 (C), U1.11 (GPIO8)
UART1_TX_SHIFT: JP6.3 (B), Q5.2 (S), R52.2
system_SPI_CS: JP4.3 (B), Q3.2 (S), R50.2, U1.29 (GPIO22)
system_SPI_CS_SHIFT: J4.4, JP4.2 (C)

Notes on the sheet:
DSUB for FC connection

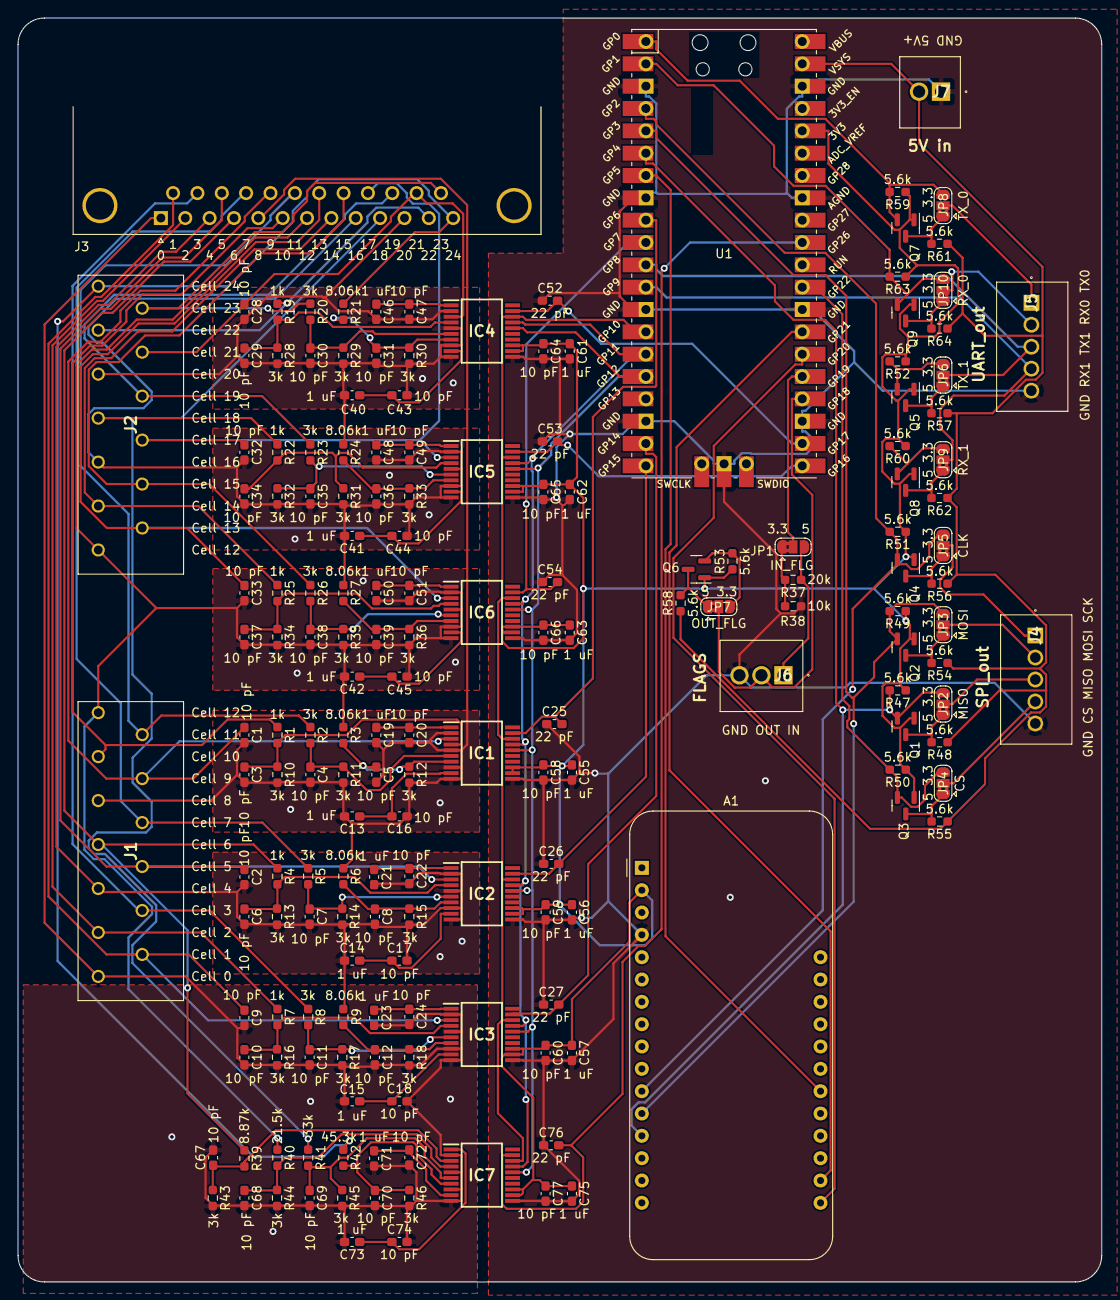
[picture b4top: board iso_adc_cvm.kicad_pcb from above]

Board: 2 copper layers, 123.2 x 143.8 mm, 176 parts (0 on the bottom side), 107 nets.

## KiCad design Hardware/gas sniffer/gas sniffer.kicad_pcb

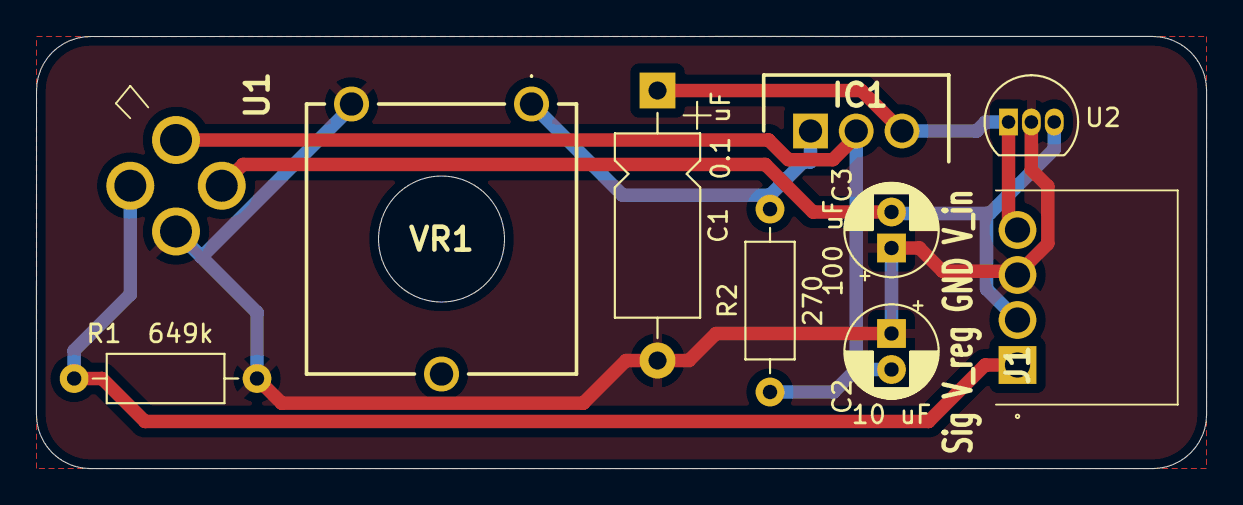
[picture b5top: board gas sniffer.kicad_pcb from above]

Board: 2 copper layers, 65.0 x 24.0 mm, 10 parts (0 on the bottom side), 6 nets.

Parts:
C1: 0.1 uF; CP_Axial_L10.0mm_D4.5mm_P15.00mm_Horizontal
C2: 10 uF; CP_Radial_D5.0mm_P2.00mm
C3: 100 uF; CP_Radial_D5.0mm_P2.00mm
IC1: LM317MBTG; TO254P482X997X2018-3P
J1: Conn_01x04; 1963447
R1: 649k; R_Axial_DIN0207_L6.3mm_D2.5mm_P10.16mm_Horizontal
R2: 270; R_Axial_DIN0207_L6.3mm_D2.5mm_P10.16mm_Horizontal
U1: SGAS701
U2: LM2931AZ-5.0_TO92; TO-92_Inline
VR1: PT15NV15-102A1010-S; PT15NV15102A1010S

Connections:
GND: C1.2, C2.1, C3.1, J1.3, R1.1, U1.3, U2.2, VR1.E1
unnamed: C2.2, IC1.2, R2.1, U1.1
unnamed: IC1.1, R2.2, VR1.A1
VDD: C1.1, IC1.3, J1.4, U2.1
V_out: J1.1, R1.2, U1.4
V_reg: C3.2, J1.2, U1.2, U2.3

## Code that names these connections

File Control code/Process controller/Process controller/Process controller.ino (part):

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//Adafruit_PWMServoDriver pwm = Adafruit_PWMServoDriver(0x40, Wire);

//Pin definitions
#define CTHD_FLW_SIG_PIN A0
#define P_1_SIG_PIN A1
#define P_2_SIG_PIN A2
#define P_3_SIG_PIN A3
#define P_4_SIG_PIN A4
#define P_5_SIG_PIN A5
#define P_6_SIG_PIN A6
#define P_7_SIG_PIN A7
#define P_8_SIG_PIN A8
#define AND_FLW_SIG_PIN A9
#define AND_FLW_SIG2_PIN A10

#define CTHD_HTR_SFTY_TC1_DRDY 22
#define CTHD_HTR_SFTY_TC1_FLT 23
#define CTHD_HTR_SFTY_TC1_CS 24
#define CTHD_HTR_SFTY_TC2_DRDY 25
#define CTHD_HTR_SFTY_TC2_FLT 26
#define CTHD_HTR_SFTY_TC2_CS 27
#define CTHD_HTR_SFTY_TC3_DRDY 28
#define CTHD_HTR_SFTY_TC3_FLT 29
#define CTHD_HTR_SFTY_TC3_CS 30

const uint8_t CTHD_HTR_SFTY_DRDY[3] = { CTHD_HTR_SFTY_TC1_DRDY, CTHD_HTR_SFTY_TC2_DRDY, CTHD_HTR_SFTY_TC3_DRDY };
const uint8_t CTHD_HTR_SFTY_FLT[3] = { CTHD_HTR_SFTY_TC1_FLT, CTHD_HTR_SFTY_TC2_FLT, CTHD_HTR_SFTY_TC3_FLT };
const uint8_t CTHD_HTR_SFTY_CS[3] = { CTHD_HTR_SFTY_TC1_CS, CTHD_HTR_SFTY_TC2_CS, CTHD_HTR_SFTY_TC3_CS };

#define AND_TRC_HTR 31
#define CTHD_TRC_HTR 32
#define CTHD_HTR 34
#define HMD_FEED_PUMP_PIN 35
#define CTHD_HMD_FEED_VLV 36
#define AND_HMD_FEED_VLV 37
#define AND_FLW_PURGE 38
#define AND_FLW_VLV_OFF 39
#define CTHD_SLND 40
#define AND_H2_SLND 41
#define AND_N2_SLND 42
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#define IPU_FLG 3

//PWM driver definitions
#define CLNT_PUMP_PWM 0
#define AND_FLW_CONT_PWM 1
#define AND_RECIRC_PWM 2
#define CTHD_VLV_PWM 3
const uint8_t CLNT_FN_PWMS[6] = { 4, 5, 6, 7, 8, 9 };

//Definitions for calculations
#define num_cells 24
#define Moles_per_litre_x_F_const_x_electrons_per_mole 8615

const uint8_t P_sig_pins[8] = { P_1_SIG_PIN, P_2_SIG_PIN, P_3_SIG_PIN, P_4_SIG_PIN, P_5_SIG_PIN, P_6_SIG_PIN, P_7_SIG_PIN, P_8_SIG_PIN };  //Array of Pressure signal inputs
uint8_t P_sig_flags = 0;                                                                                                                   //Flags representing if pressure signals are detected. 1 means sensor detected on that pin, 0 means no sensor detected
uint32_t P_readings[5] = { 0, 0, 0, 0, 0 };

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  uint16_t AND_FLW_value[2] = { 0 };                    //SmLPM
  uint16_t CTHD_FLW_output = 0;                       //12 bit PWM value
  uint16_t AND_FLW_target = 0;                          //SmLPM
  uint16_t AND_recirc_PWM = 0;                          //12 bit PWM value
  uint16_t CLNT_FLW_output = 0;                         //Coolant pump 12 bit PWM value
  bool CTHD_HTR = 0;                                    //is the cathode heater on/off
  uint8_t Valves = 0;                                   //Bit flags for what valves are set. Order is anode humidifier feed, cathode humidifier feed, anode flow controller purge, anode flow controller valve, anode purge, H2 in, N2 in
  uint32_t Process_controller_timestamp = 0;            //timestamp in mS that data was sent out
} Outgoing_data;
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    }
  }

  if (analogRead(CTHD_FLW_SIG_PIN) < Cathode_flow_sensor_minimum_threshold) {  //Flow sensor should output a minimum of 4mA, which should be read as 1V. Threshold of 190=0.928V
    FaultSend(Interface, 'f', 0x21, 0x01);                                     //if reading is outside nominal, send out fault code
    FaultSend(DataLogger, 'f', 0x21, 0x01);
    if (Serial) {
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
  //EDITME add code to test other outputs one by one?

  pinMode(AND_FLW_PURGE, OUTPUT);
  digitalWrite(AND_FLW_PURGE, HIGH);  //Purge line high = normal operation, low = purge
  pinMode(AND_FLW_VLV_OFF, OUTPUT);
  digitalWrite(AND_FLW_VLV_OFF, LOW);                             //Off line high = normal operation, low = closed valve
  AND_FLW_reading[1] = analogRead(AND_FLW_SIG_PIN);               //Voltage output from flow controller
  AND_FLW_reading[2] = analogRead(AND_FLW_SIG2_PIN);              //Current output from flow controller
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  Outgoing_data.AND_FLW_value[2] = map(AND_FLW_reading[2], 0, 1023, 0, 50000);  //Convert analogue reading to mL per minute
  //EDITME Write some code to test if the flow controller is working

  pinMode(AND_TRC_HTR, OUTPUT);
  pinMode(CTHD_TRC_HTR, OUTPUT);
  pinMode(CTHD_HTR, OUTPUT);
}

void loop() {
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


  Outgoing_data.CTHD_FLW= map(analogRead(CTHD_FLW_SIG_PIN), 204, 1023, 0, 500);


  if (millis() - HIH_last_read_time > HIH_interval) {  //HIH takes up to 50 mS to convert, so for speed/non blocking, cycle triggers next conversion immediately after reading
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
